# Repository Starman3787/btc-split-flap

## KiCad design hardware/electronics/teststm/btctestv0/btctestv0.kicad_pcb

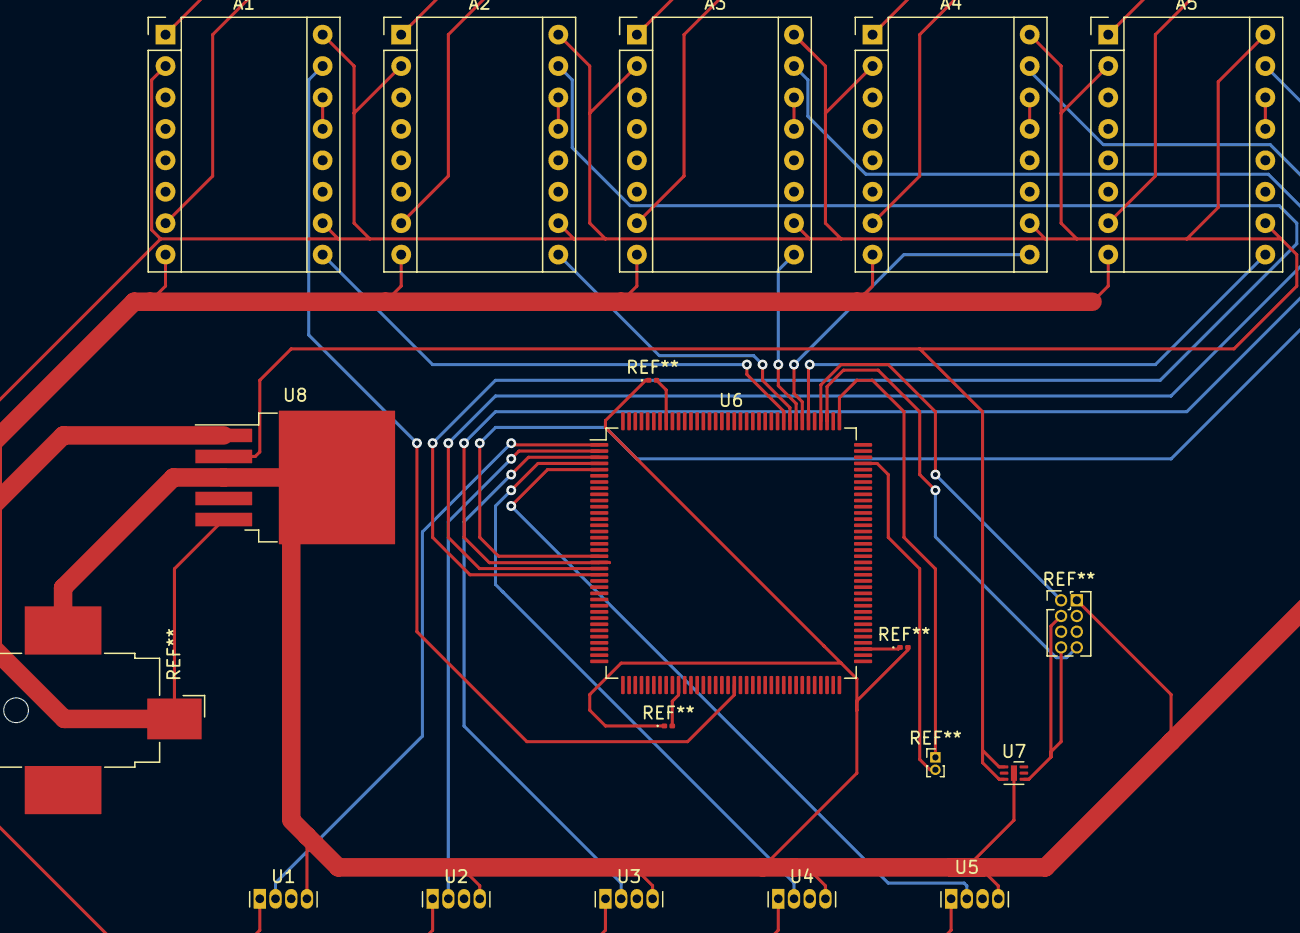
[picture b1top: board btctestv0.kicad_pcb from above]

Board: 2 copper layers, 13 parts (0 on the bottom side), 23 nets.

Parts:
A1, A2, A3, A4, A5: Pololu_Breakout_A4988; Pololu_Breakout-16_15.2x20.3mm
U1, U2, U3, U4, U5: A1363xKTTN-1; Allegro_SIP-4
U6: STM32F767ZITx; LQFP-144_20x20mm_P0.5mm
U7: MIC5353-3.3YMT; MLF-6-1EP_1.6x1.6mm_P0.5mm_EP0.5x1.26mm
U8: GL2576-5.0TA5R; TO-263-5_TabPin3

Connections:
+5V: A1.2, A1.10, A1.16, A2.2, A2.10, A2.16, A3.2, A3.10, A3.16, A4.2, A4.10, A4.16, A5.2, A5.10, A5.16, U1.1, U2.1, U3.1, U4.1, U5.1, U7.1, U7.3, U8.2
+12V: A1.8, A2.8, A3.8, A4.8, A5.8, U8.1, U8.5
GND: A1.1, A1.7, A2.1, A2.7, A3.1, A3.7, A4.1, A4.7, A5.1, A5.7, U1.4, U2.4, U3.4, U4.4, U5.4, U7.2, U7.7, U8.3
HES_0: U1.2, U6.1
HES_1: U2.2, U6.2
HES_2: U3.2, U6.3
HES_3: U4.2, U6.4
HES_4: U5.2, U6.5
MOT_0_EN: A5.9, U6.114
MOT_0_STEP: A5.15, U6.19
MOT_1_EN: A4.9, U6.115
MOT_1_STEP: A4.15, U6.20
MOT_2_EN: A3.9, U6.116
MOT_2_STEP: A3.15, U6.21
MOT_3_EN: A2.9, U6.117
MOT_3_STEP: A2.15, U6.22
MOT_4_EN: A1.9, U6.118
MOT_4_STEP: A1.15, U6.55
unnamed: A1.13, A1.14
unnamed: A2.13, A2.14
unnamed: A3.13, A3.14
unnamed: A4.13, A4.14
unnamed: A5.13, A5.14

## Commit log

2021-05-22 Create flap.dxf~
2021-05-27 create delay function
2021-05-27 add CMSIS drivers
2021-05-27 add STM32F76 headers
2021-05-27 Create Makefile
2021-05-27 initialise systick function
2021-05-27 systick interrupt handler
2021-05-27 add function to toggle motors on and off
2021-05-27 remove commented out code
2021-05-27 fix hall effect sensor read and init functions
2021-05-27 fix motor enable/disable function
2021-05-27 only spin motors if sensor 1 detects a magnet
2021-05-27 properly unset bits
2021-05-27 add commenting
2021-05-27 add wifi file
2021-05-29 update to allow for 6 complete spools with attachments
2021-05-29 update spool attachment to improve spacing with spools and cards
2021-05-29 add license
2021-05-29 remove obsolete files
2021-05-29 move pin mappings to header files
2021-06-01 create uart files
2021-06-02 add uart driver
2021-06-02 update hall effect sensor pins
2021-06-02 wifi test
2021-06-02 add uart read and write functions
2021-06-08 call wifi and uart init
2021-06-08 fix careless mistakes and add commenting
2021-06-08 remove pointer
2021-06-08 add function to read full uart string
2021-06-08 Update Makefile
2021-06-08 add function to write a sting to the uart
2021-06-09 add additional uart pins for logging
2021-06-09 add led driver
2021-06-09 cleanup
2021-06-09 add extra uart for logging
2021-06-09 correct typo
2021-06-09 add function to read everything received and check it against a provided string, and fixed an issue for writing a full string to uart
2021-06-09 fixed an issue for writing full string to uart
2021-06-09 add wifi init and test command
2021-06-09 init led
2021-06-10 add function to output string over uart for debugging
2021-06-10 tidy
2021-06-10 add wifi functions
2021-06-19 remove unsafe read function
2021-06-19 remove nostdlib
2021-06-19 properly declare dynamic memory
2021-06-25 make side-specific panels
2021-06-25 check if parts slot together
2021-06-25 change line colour to red
2021-06-26 fix + optimise read_full_uart_until_json_property_match function
2021-06-26 create fetch_price function, to fetch price with max char length
2021-06-26 return price as uint32 rather than a char *
2021-06-26 add standard status functions
2021-06-26 use standard status functions
2021-06-26 function to toggle an led
2021-06-27 clear ok pin on error
2021-06-27 improve error handling and simplified some expressions
2021-06-27 add setup instructions
2021-06-30 corrected base/top width
2021-06-30 update to correct top
2021-07-11 add functions for interaction with split-flap modules
2021-07-12 dont include stdlib.h
2021-07-12 adjust dimensions
2021-07-14 add lots of commenting
2021-07-17 rearrange files
2021-07-25 update pins
2021-07-25 deal with strings in terms of pointers, rather than arrays
2021-07-26 prevent initial position from being stuck at 0
2021-07-26 create find_pattern function
2021-07-26 return 0U on error
2021-07-26 improve variable name
2021-07-26 change type to 32 bit unsigned int
2021-07-26 increase wait time to allow module to connect to wifi
2021-07-26 wait for full response before proceeding
2021-07-26 log pattern finding
2021-07-28 wait for wifi module to connect instead of having a blind delay
2021-08-03 add parse_date function
2021-08-03 add function to convert hexidecimal to denary
2021-08-03 add timeout to the read_uart function
2021-08-03 move find_pattern to uart.c
2021-08-03 add unix time handling
2021-08-03 add http functions
2021-08-03 add http parser entry point
2021-08-03 define unix
2021-08-03 use init_esp_01s() in preference to init_wifi()
2021-08-05 account for sensor having larger than intended detection range
2021-08-14 split into modes
2021-08-14 simplify api
2021-08-14 add free functions
2021-08-14 remove chunked encoding (and use http/1.0 instead)
2021-09-01 replace leading underscores with trailing underscores
2021-09-01 reduce use of malloc
2021-09-01 remove dynamically allocated memory
2021-09-02 remove more malloc and replace with structures of a fixed size
2021-09-03 remove more dynamically allocated memory and made changes which improve the overall security
2021-09-04 cleanup + improve error handling & security
2021-09-08 add escape sequence to end of output
2021-09-11 add debug logging
2021-09-11 use unsigned postfix
2021-09-11 calculate request size
2021-10-01 add microstepping
2021-10-09 add pcb
2021-10-17 notify of error
2021-10-17 change baud rate to 115200
2021-10-17 simplify main loop
2021-10-17 fix some timing issues
2022-06-02 add custom mode
2022-06-02 improve handling of uart
2022-06-02 update to use custom software on esp01s
2024-01-09 update cad
2024-01-23 ensure code works when number of flaps is changed
